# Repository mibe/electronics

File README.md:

# This repo contains some electronic projects of mine:

## Arduino
Some simple codes for the Arduino platform

## Blaulicht
Retrofitting an old toy car with emergency lights

## BreadBoard-Power-BusBar
Connect both opposing supply rails of a breadboard in an orderly fashion

## breakout_boards
Some breakout boards for use on a breadboard

## cookie-mouse
An automatic clicking mouse for the game Cookie Clicker

## Feuermelder
A USB "keyboard" disguised in the form of a fire call point to open the Windows Taskmanager

## Flip-USB
A replacement USB board for JBL's Flip 2 bluetooth speaker

## LCR-Shoe
A power supply attachment for cheap LCR meters

## StarPower
A control PCB for a christmas star as a replacement for the old, less energy-efficient one

## thunder-timer
A device to calculate thunderstorm distance by timing the interval between lightning and thunder

## tiny-UPDI-burner
A small board for connecting an USB to RS-232 converter to SOIC to DIL converters for burning ATtiny's via UPDI

## uCurrentCase
A case for Dave Jones' µCurrent GOLD

## USB-breaker
A tool to shortly disconnect a USB device from the USB bus

## Wire-to-RJ14
A simple adapter to connect bare wires to a cable with RJ-14 connectors

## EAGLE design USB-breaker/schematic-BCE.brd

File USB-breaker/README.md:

# USB-breaker
This is a tool to shortly disconnect a USB device from the USB bus. This is done by switching two relays, which are tied into the USB bus. One relay switches the data lines, the other the power supply lines. A RC filter tries to mimic the unplugging of a USB type A connector: Due to the design of this connector, the data lines are disconnected before the power lines.

This tool is mainly used for developing USB devices: A reset is now possible without unplugging the USB connector of the device. Hence it is saving insertion-removal cycles of the hub's USB connector: The standard A type connector has a designed lifetime of 1.500 cycles (see "Universal Serial Bus Cables and Connectors Class Document", table 3-1).

## BOM

### PCB
See the ```BOM-PCB.csv``` file. Short summary:

* 2 capacitors
* 2 diodes
* 1 pin header
* 2 relays
* 5 resistors
* 2 transistors
* 5 connectors

### The rest
* Case KEMO G025
* Red LED, 3 mm diameter
* SPST switch (on/off switch)
* Push button, normally open
* Some wires
* Four 5 mm spacer bolts
* Four M3 5 mm screws

## Enclosure
The top half of the case is used as front panel, where the controls and indicator LED are mounted. See ```drilling plan.pdf``` for a drawing of the drill holes. 

## Limitations
This tool is not designed to work with high-current USB devices. It is designed for a standard USB device with draws 500 mA at maximum. Don't hook up a device which draws more current (like a phone, charger, fan or vacuum cleaner)! The rated load of the relay contacts is 1 A, though.

## Design & building remarks
* If you don't have an SPST switch, you can use any other and just leave the remaining pole(s) unconnected.
* It was planned to connect the front panel with ribbon cable & an IDC connector mating with ```SV1```. But that didn't work, because the switch got in the way. Use a case which is at least 1.5 cm higher.
* Use the -ECB.brd / -ECB.sch files if you have transistors with a different pinout.

## License
GNU GPL v2 (see LICENSE.txt and firmware/usbdrv/License.txt)

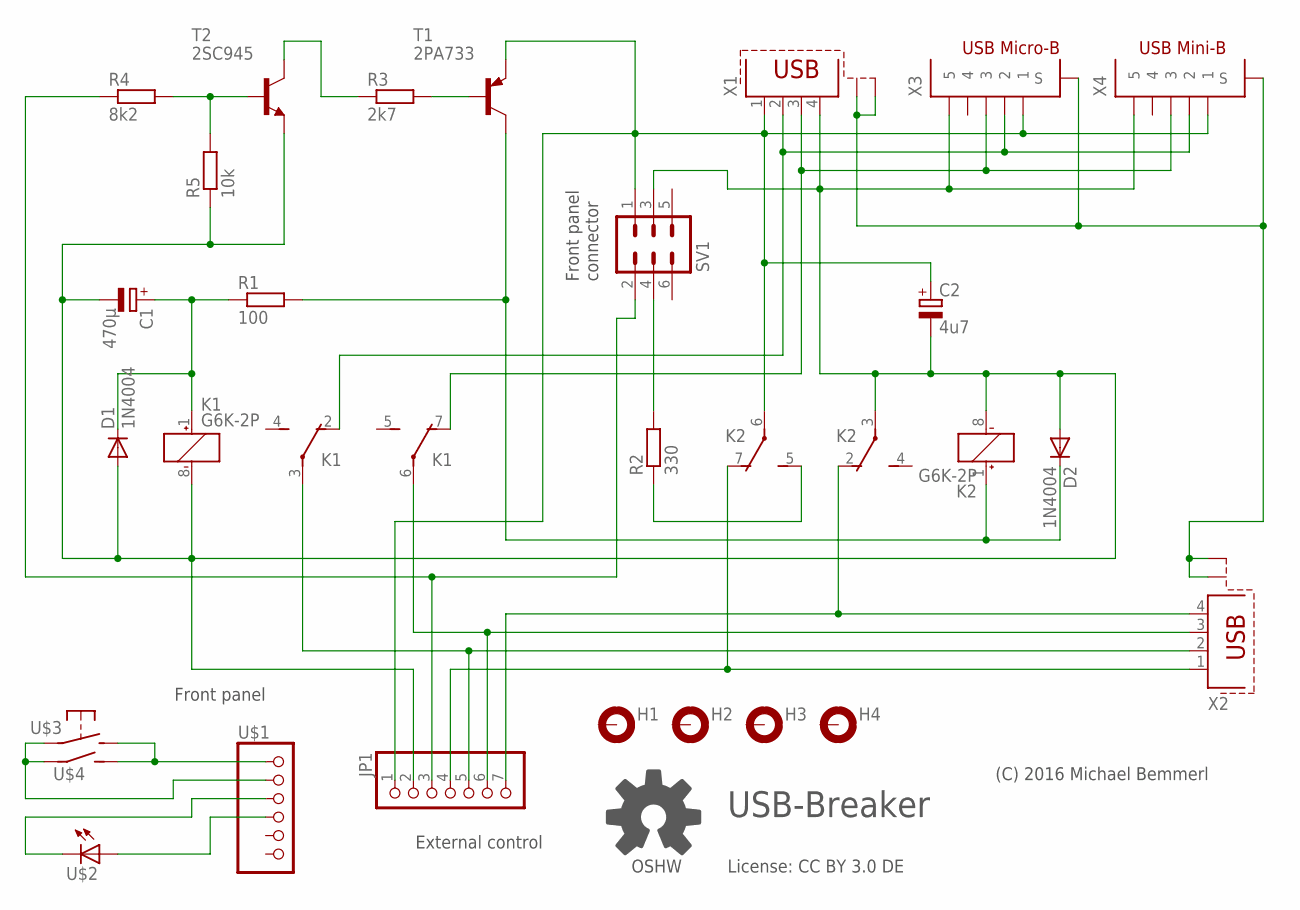
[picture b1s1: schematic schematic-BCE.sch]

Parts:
C1: 470µ; E3,5-8
C2: 4u7; E2,5-6
D1, D2: 1N4004; DO41-10
H1, H2, H3, H4: MOUNT-PAD-ROUND3.0; 3,0-PAD
JP1: PINHD-1X7/90; 1X07/90
K1, K2: G6K-2P
R1: 100; 0207/10
R2: 330; 0207/10
R3: 2k7; 0207/10
R4: 8k2; 0207/10
R5: 10k; 0207/10
SV1: ML6
T1: 2PA733; TO92-BCE
T2: 2SC945; TO92-ECB
X1: PN61729-S
X2: PN87520-S
X3: 10104110; 10104110-0001LF
X4: UX60SC-MB-5ST

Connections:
D+_IN: K1.7 (O), X1.3, X3.P$3 (3), X4.P$3 (3)
D+_OUT: JP1.6, K1.6, X2.3
D-_IN: K1.2 (O), X1.2, X3.P$2 (2), X4.P$2 (2)
D-_OUT: JP1.5, K1.3, X2.2
ENABLE: D2.C, K2.1 (+), R1.2, T1.C
EXTERNAL_ENABLE: JP1.3, R4.1, SV1.2
GND_IN: C1.-, C2.-, D1.A, D2.A, JP1.2, K1.8 (-), K2.3, K2.8 (-), R5.1, SV1.3, T2.E, X1.4, X3.P$5 (5), X4.P$5 (5)
GND_OUT: JP1.7, K2.2 (O), X2.4
LED: R2.2, SV1.4
unnamed: R3.2, T1.B
unnamed: R3.1, T2.C
unnamed: R4.2, R5.2, T2.B
unnamed: C1.+, D1.C, K1.1 (+), R1.1
SHIELD: X1.S1, X1.S2, X2.S1, X2.S2, X3.P$6 (S), X3.P$7 (S), X4.P$6 (S), X4.P$7 (S)
VCC_IN: C2.+, JP1.1, K2.6, SV1.1, T1.E, X1.1, X3.P$1 (1), X4.P$1 (1)
VCC_LED: K2.5 (S), R2.1
VCC_OUT: JP1.4, K2.7 (O), X2.1

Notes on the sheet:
Front panel
Front panel connector
External control
OSHW
(C) 2016 Michael Bemmerl
License: CC BY 3.0 DE
USB-Breaker

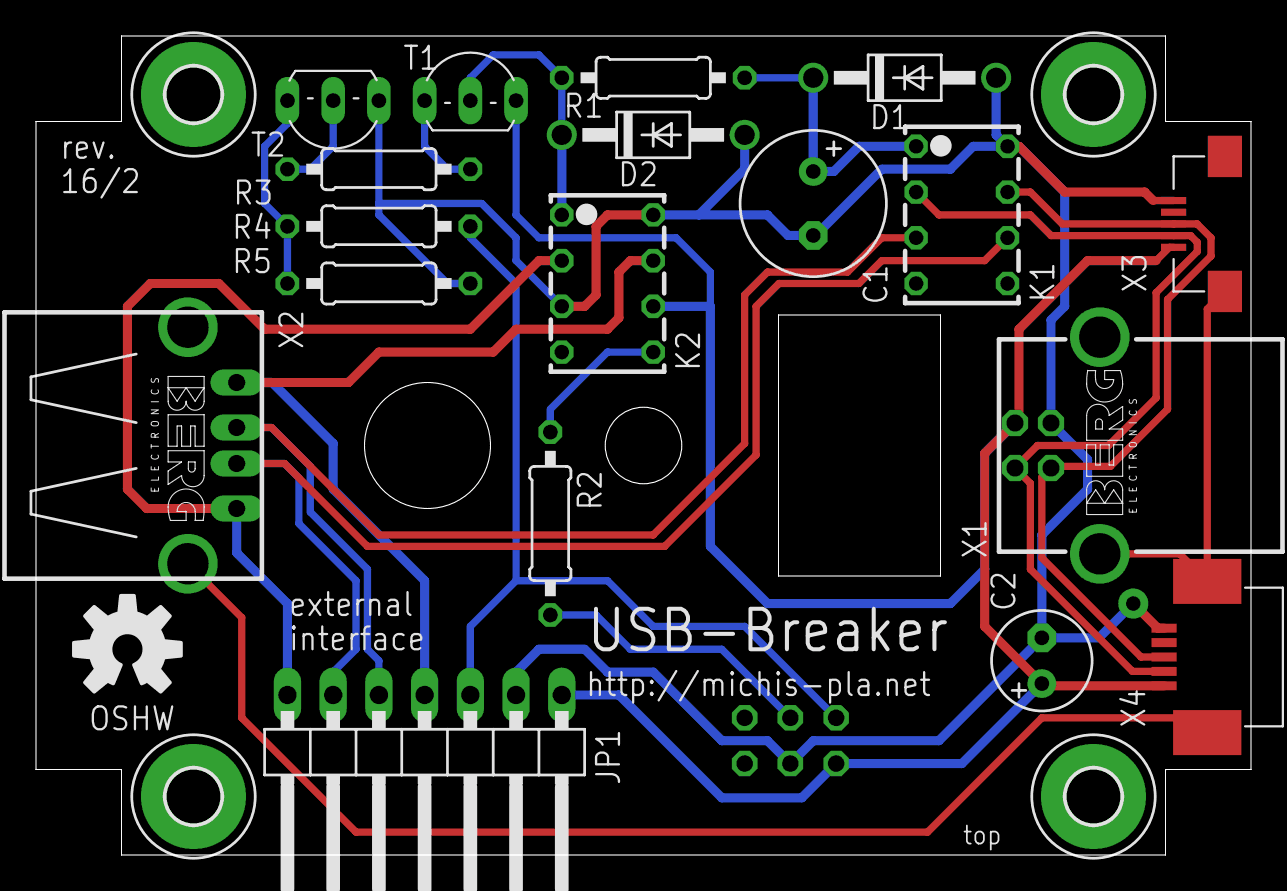
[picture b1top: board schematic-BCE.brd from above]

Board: 2 copper layers, 67.5 x 45.5 mm, 23 parts (1 on the bottom side), 17 nets.

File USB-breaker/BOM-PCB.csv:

"Part";"Value";"Device";"Package";"Description"
"C1";"470µ";"CPOL-EUE3.5-8";"E3,5-8";"POLARIZED CAPACITOR, European symbol"
"C2";"4u7";"CPOL-EUE2.5-6";"E2,5-6";"POLARIZED CAPACITOR, European symbol"
"D1";"1N4004";"1N4004";"DO41-10";"DIODE"
"D2";"1N4004";"1N4004";"DO41-10";"DIODE"
"H1";"MOUNT-PAD-ROUND3.0";"MOUNT-PAD-ROUND3.0";"3,0-PAD";"MOUNTING PAD, round"
"H2";"MOUNT-PAD-ROUND3.0";"MOUNT-PAD-ROUND3.0";"3,0-PAD";"MOUNTING PAD, round"
"H3";"MOUNT-PAD-ROUND3.0";"MOUNT-PAD-ROUND3.0";"3,0-PAD";"MOUNTING PAD, round"
"H4";"MOUNT-PAD-ROUND3.0";"MOUNT-PAD-ROUND3.0";"3,0-PAD";"MOUNTING PAD, round"
"JP1";"";"PINHD-1X7/90";"1X07/90";"PIN HEADER"
"K1";"G6K-2P";"G6K-2P";"G6K-2P";"Low Signal Relay"
"K2";"G6K-2P";"G6K-2P";"G6K-2P";"Low Signal Relay"
"R1";"100";"R-EU_0207/10";"0207/10";"RESISTOR, European symbol"
"R2";"330";"R-EU_0207/10";"0207/10";"RESISTOR, European symbol"
"R3";"2k7";"R-EU_0207/10";"0207/10";"RESISTOR, European symbol"
"R4";"8k2";"R-EU_0207/10";"0207/10";"RESISTOR, European symbol"
"R5";"10k";"R-EU_0207/10";"0207/10";"RESISTOR, European symbol"
"SV1";"";"ML6";"ML6";"HARTING"
"T1";"BC558B";"BC558B-PNP-TO92-EBC";"TO92-EBC";"PNP Transistror"
"T2";"BC548B";"BC548-NPN-TO92-CBE";"TO92-CBE";"NPN Transistror"
"X1";"PN61729-S";"PN61729-S";"PN61729-S";"BERG USB connector"
"X2";"PN87520-S";"PN87520-S";"PN87520-S";""
"X3";"10104110";"10104110";"10104110-0001LF";"10104110 - Micro USB B Type Receptacle"
"X4";"UX60SC-MB-5ST";"UX60SC-MB-5ST";"UX60SC-MB-5ST";"UX60S Series - Mini-B Connectors, SMT mount receptacles meeting requirements of USB 2.0 Standard"

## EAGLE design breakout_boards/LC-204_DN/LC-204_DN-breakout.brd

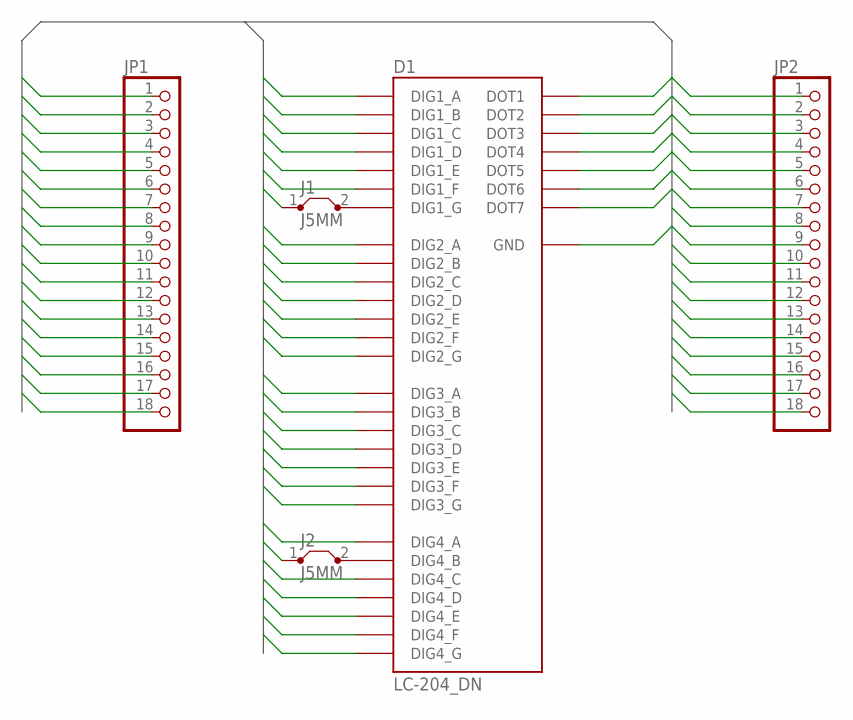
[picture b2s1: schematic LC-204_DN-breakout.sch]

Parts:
D1: LC-204_DN
J1, J2: J5MM; 05
JP1, JP2: PINHD-1X18; 1X18

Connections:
DIG1_1: D1.DIG1_A, JP2.4
DIG1_2: D1.DIG1_B, JP2.5
DIG1_3: D1.DIG1_C, JP1.4
DIG1_4: D1.DIG1_D, JP1.3
DIG1_5: D1.DIG1_E, JP1.2
DIG1_6: D1.DIG1_F, JP2.3
DIG1_7: J1.1, JP2.2
DIG2_1: D1.DIG2_A, JP2.8
DIG2_2: D1.DIG2_B, JP2.9
DIG2_3: D1.DIG2_C, JP1.7
DIG2_4: D1.DIG2_D, JP1.6
DIG2_5: D1.DIG2_E, JP1.5
DIG2_6: D1.DIG2_F, JP2.7
DIG2_7: D1.DIG2_G, JP2.6
DIG3_1: D1.DIG3_A, JP2.12
DIG3_2: D1.DIG3_B, JP2.13
DIG3_3: D1.DIG3_C, JP1.12
DIG3_4: D1.DIG3_D, JP1.11
DIG3_5: D1.DIG3_E, JP1.9
DIG3_6: D1.DIG3_F, JP2.11
DIG3_7: D1.DIG3_G, JP1.10
DIG4_1: D1.DIG4_A, JP2.16
DIG4_2: J2.1, JP2.17
DIG4_3: D1.DIG4_C, JP1.16
DIG4_4: D1.DIG4_D, JP1.15
DIG4_5: D1.DIG4_E, JP1.14
DIG4_6: D1.DIG4_F, JP2.15
DIG4_7: D1.DIG4_G, JP2.14
DOT1: D1.DOT1, JP2.1
DOT2: D1.DOT2, JP1.1
DOT3: D1.DOT3, JP2.10
DOT4: D1.DOT4, JP1.8
DOT5: D1.DOT5, JP1.13
DOT6: D1.DOT6, JP2.18
DOT7: D1.DOT7, JP1.17
GND: D1.GND, JP1.18
unnamed: D1.DIG1_G, J1.2
unnamed: D1.DIG4_B, J2.2

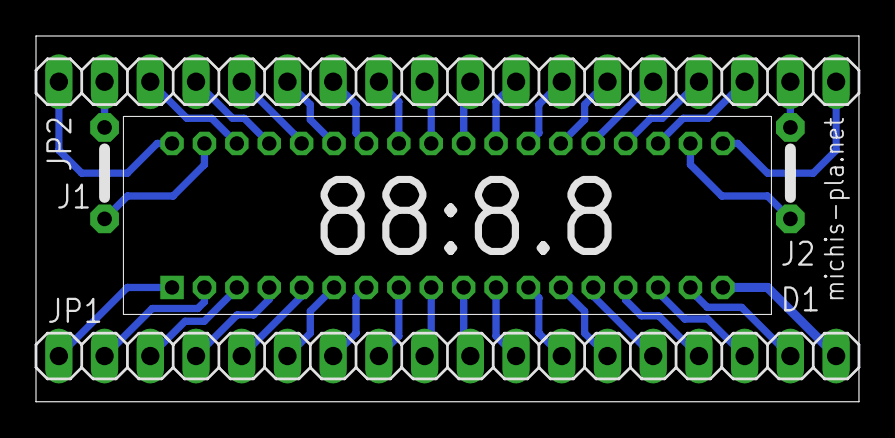
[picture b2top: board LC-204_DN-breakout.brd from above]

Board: 2 copper layers, 45.7 x 20.3 mm, 5 parts (0 on the bottom side), 38 nets.

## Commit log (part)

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2012-10-24 Two types of blinking (static / random)
2012-10-24 Moved definitions into separate header file.
2012-10-27 Another blink mode, this time on and off time are random.
2012-10-27 Updated .gitignore to ignore AVR Studio workspace files (*.aws).
2012-11-18 Added schematics.
2013-01-26 Web frontend supports more than one sensor
2013-01-27 Output temperature on LCD via RS-232
2013-01-27 Interrupt logic for button; Moved LCD pins to < 10, because >= 10 is SPI for Ethernet shield
2013-01-27 Fixed delay logic (overflow)
2013-01-27 Read VCC for use in calculation of LM35 value
2013-01-31 Reactivated ethernet functions. This should be it for the 2013 version of this project.
2013-08-26 All EEVblog episodes with youtube URLs
2014-03-24 EEVblog YouTube episode URLs updated
2015-05-10 Added V-USB driver from release 20121206
2015-05-15 Working Makefile & USB config
    Both were generated by the make-file.sh script
2015-05-16 Use the calibration routine for the RC oscillator.
2015-05-16 Changed Makefile for specific ATTiny45 configuration.
2015-05-17 Removed the demo circle function and added code for activating the mouse button depending on the switch state.
2015-05-31 Use Timer1 overflow for activating the mouse button
2015-06-07 Bugfix: Prevent the disabling of Timer1 when the ADC value is too low.
2015-06-07 Use the full scale of the potentiometer in the ADC IRQ.
2015-06-08 Mostly license stuff
2015-06-09 Added README and circuit diagram.
2015-06-10 Tested with Linux kernel OS
2015-06-10 Added switch and push button, connected to ground.
2015-06-11 Screenshot of the circuit diagram
2015-12-06 Replaced K1 & K2 relay G6K-RF with G6K-2P. SMD --> THT
2016-01-23 Display only pin names in symbol UX60S.
2016-01-24 Using shielded A connectors now.
2016-01-24 Bugfix: Connect the delayed relay to GND_IN instead of the (already disconnected off) GND_OUT.
2016-01-24 Completed front panel components.
2016-02-16 New external control interface as pin header.
2016-02-16 Switching of the relays is done upstream with transistors.
    Also finished connecting nets to the external interface connector.
2016-02-19 The schematic is now pretty much done:
    - Library update
    - Values for the two transistors
2016-02-20 Added last details:
    - Name / Copyright / License
    - OSHW logo
    - Processed all warnings in the ERC
    Boy, this schematic looks ugly. I'm better using a DIN A4 frame next time...
2016-02-21 Basic PCB dimensioning
2016-02-23 First parts placed
2016-03-02 NAME and VALUE on wrong layer
2016-03-06 Shield pins of both USB connectors are marked as internally connected.
2016-03-06 PCB layout, part one
2016-03-08 Added signal classes for USB data and power.
2016-03-11 Added VCC_OUT & GND_OUT to power signal class
2016-03-13 Changed text ratio.
2016-03-13 Say hello to Mr. Ground Plane!
2016-03-20 Breakout board for a Rohm LC204 DN LED 7-segment display.
2016-04-23 Value of R1 changed from 120 Ω to 100 Ω. Otherwise the voltage for relay K1 is too low.
2016-04-23 T1 is now used from another library. BCE was wrong, ECB is the right package.
2016-04-24 The first assembly pics.
2016-04-30 Added code from V-USB HIDKeys example, release 2012-12-08.
2016-05-01 Changed USB settings:
    - using pid.codes' test PID
    - correct report descriptor length
    - changed device name
    - using INTR_POLL_INTERVAL from HIDKeys example
2016-05-09 Don't call buildReport on USBRQ_HID_GET_REPORT - just relay the previous generated one.
2016-05-10 Removed unused #define's and converted spaces used as indentation to tabs.
2016-05-10 License stuff
2016-05-10 Added a README.md.
2016-05-10 PID 0xF12E got assigned by pid.codes. Thanks!
2016-06-02 Bugfix: USB D- was wrongly connected to PB1 instead of PB2.
2016-06-08 Updated screenshot of Feuermelder schematic
2016-06-11 Added README and BOM.
2016-06-11 Added two photographs of the finished device.
2016-06-11 Updated the README.
2018-01-03 New device: MTCH101 (touch sensor IC)
2018-01-14 New device: TS3USB30E (High-Speed USB 2.0 Multiplexer)
2018-01-30 Who the hell thought it would be a good idea to force net names on pins marked as sup?
2018-02-05 New device: CLP6C RGB LED
2018-03-02 Fixed layer
2018-06-03 Looks like the timing algorithm is working.
2018-07-06 Moved Eagle CAD library to new folder and added a KiCad library.
2018-07-09 The schematic should be complete now.
2018-07-13 Added courtyard for part SW_Push_10mm.
2018-07-14 Added ground plane
2018-08-01 Readme and license stuff
2018-08-08 Oops, debugging stuff was still in the code.
2018-08-08 Added comments
2018-08-19 That should be it for the schematic.
2018-08-25 The makefile...
2018-08-26 Added a reset switch.
2018-08-27 Renamed nets to some saner names.
2018-09-02 Finished the layout
2018-09-15 I got the pin-out of Q1 wrong: It's ECB not BCE!
2018-09-22 Added more documentation.
2018-09-29 Added some pictures
2018-10-08 Unlisted videos on EEVblog2
2019-05-05 Update files to KiCad 5
2019-05-11 Fixed update to KiCad 5.
    Well, the update didn't quite work out of the box. My footprint library table was still using the KiCad 4 footprints.
2019-05-27 Added a DC/DC converter to power the buzzer.
    The nominal battery voltage of 2.4 is too less for adequately powering the 5 volt buzzer. The converter provides provides 5 volt exclusively for the buzzer and is enabled by the microcontroller.
2019-06-10 Updated PCB rendering to current revision
2019-06-14 Deactivated the BOD again.
    Well, that didn't quite work out: The BOD was erroneously triggered during activation of the buzzer. The input voltage probably had a transient which caused the trigger.
2019-06-23 Beep every kilometer when counting.
    This implements #3.
2019-09-10 Bunch o' footprints:
    - USB connectors
    - Battery contacts / holders
2019-10-16 Renamed some nets and added mounting holes.
2019-10-19 Renamed to add suffix CircularHoles.
2019-10-26 Marker of the PCB edge
2019-10-26 Import of the Aisler 2 layer template
2019-10-30 Routing and positioning of the silk screen elements is finished
2019-11-08 Removed unnecessary traces.
2019-11-11 Updated netlist
2020-01-18 Better description of the Keystone parts.
    The polarity is depending on how this connector is used.
    (cherry picked from commit 02e73c2f822f0898dfba0953576ab4aaca45f917)
2020-01-18 Rotated the Anti-Rotation Dimples by 45° clockwise.
    The datasheet states that the location is random, but all reference material I could find suggest that the dimples are 45° rotated to the datasheet version.
    (cherry picked from commit 67bc0c7df24bde9f7f3c4ad2011b5573b9a0d1f6)
2020-02-02 Marker of the PCB edge
    (cherry picked from commit 13fa41d590fd288d5f026ec3b4d3241c9ee901f3)
    # Conflicts:
    # Libraries/KiCad/mibe.pretty/BatteryHolder_MPD_BA9VPC_1xPP3.kicad_mod
2020-02-06 The footprints landed in the official KiCad footprint repository.
2020-02-18 Added BOM and "Characteristics" field for for more detail.
2020-02-18 Update LCR-Shoe.csv
    Let's see if GitHub displays this nice and beautiful...
2020-02-18 Update index
2020-02-19 USB B Lumberg 2411 02 updates
    Fixed Fab / Silk / CrtYrd layers, added 3D reference and prettified description.
2020-02-27 Fixed Silk and CrtYd layer.
2020-03-01 Centered footprint to origin @ 0,0.
2020-03-03 The main circuit.
2020-03-05 Fixed Fab layer line width.
2020-03-11 Moved the PCB to have the center at 127|127.
    This should make it easier to work with inch / millimeter.
2020-03-22 Removed more merged footprints
2020-03-29 The blinking algorithm is pretty much done.
    It uses both A & B channels of Timer0 in Fast PWM mode. Both channels are connected to their Output Compare pins. The Timer0 Overflow Interrupt powers a state machine, which in turn toggles the DDR b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
    The Timer0 controls the brightness of the LEDs with PWM, and the state machine controls the blinking pattern.
2020-03-31 Enter sleep mode as soon as the interrupt handling is finished.
2020-03-31 Disable stuff to minimize power consumption.
2020-04-17 Use a CR2032 3 Volt battery as power source.
2020-04-18 Enable pull-ups on unsused inputs.
2020-04-19 Optimized the code a bit. This saves a couple of decibytes.
2020-05-13 Added Readme.md
2020-05-17 Moved the headers by about 0.5 mm.
    The previous distance was too small and the headers didn't fit properly into the breadboard.
2020-05-30 Added components to have a power status LED on the PCB.
2020-05-31 Finished placing and routing the new components for the Power indication.
2020-06-02 Added BOM.
2020-06-02 Added a readme file.
2020-06-02 Updated URL to CERN OHL v1.2 license.
2020-06-03 Open Source Hardware Logo in 2.7 x 2.5 mm size.
2020-06-08 Added a reverse protection diode.
2020-06-10 Another variant of the OSHW logo.
2020-06-19 Fix typo.
2021-02-23 Wire-to-RJ14, a board for connecting bare wires to an RJ14 connector used in POTS.
2021-08-08 Add a replacement USB board for JBL's Flip 2 bluetooth speaker.
2021-08-28 First bits of the Magic the Gathering life counter.
2021-09-07 Use Timer0 for multiplexing both 7-segment-digits.
2021-10-04 The PCB is done, except for the Silk layer.
2021-10-11 The silk layer is now done. Also added a BOM.
2021-11-03 First bits of the schematic of the PCB.
2021-11-08 Specify programming resistor and protection diode for charger.
2021-11-09 Add a voltage monitor to be used to reset the microcontroller.
    This is used as sort of a undervoltage lockout protection to protect the battery. The threshold voltage of the used IC is 3.08 V, which is near the minimum discharge voltage of a LiPo battery of 3 V.
2021-11-28 Reset circuitry
2021-11-29 Add digit multiplexing.
2021-12-08 Use a net tie for combining MOSI/MISO & DIGIT_X_ENABLE.
    MOSI/MISO are used for programming, while the DIGIT_X_ENABLE lines enable the corresponding display digit.
    That's pretty much it for the schematic. Finally.
2021-12-21 First bits of the PCB layout.
2022-07-08 Placement of (mounting) holes, 7-seg. displays and programming socket.
2022-07-18 The placing & routing is pretty much done, except GND.
2022-07-19 All references are moved to a visible location.
2022-07-19 Improved the silkscreen a bit.
2022-08-03 Add BOM HTML file.
2022-09-20 Add missing parenthesis.
    This explains the unwanted (and not programmed) behavior discussed in #10.
2022-10-08 Display sizes with percentages of used space.
2022-10-25 Prevent "afterglow" of the digits by decreasing the multiplexing speed.
    Instead of using the full clock, a prescaler of 64 is used now.
2022-10-25 Fixed various stuff:
    - The counting function now works properly (fixed #9)
    - When multiplexing the correct digit is driven
    - More comments here and there
2022-11-01 Remove R16 to fix #8.
    The chances of the battery and programmer connected at the same time is there but actually pretty low. To flash the micro-controller you would disconnect the battery because of the easier handling al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
2022-11-02 Change the USB B mini charging connector to USB C (see #6). Still needs to be placed and routed.
2022-11-12 Add first version of the schematic.
2022-11-14 Add mounting holes and the correct footprint for the push button.
2022-11-14 Starting with layout: Components which have fixed positions due to the casing are placed and locked.
2022-11-16 Bugifx: The crystal footprint had the wrong pin mapping.
2022-11-16 Finish the layout of the first revision.
2022-11-22 Add BOM
2022-11-26 Optimized the code a bit to consume less CPU cycles in Timer mode.
2022-11-27 Disable stuff to save power:
    - Enter sleep mode
    - Disable Timer0, USI, ADC, the analog comparator & digital input buffer.
    - Enable pull-ups
2022-11-27 Use Timer0 as timer instead of Timer1.
    Timer0 consumes less power than Timer1. That saves a whopping 4 µA, which is 25.6 %! This has some serious Apollo 13 vibes!
2022-11-28 Enable the pull-up on the button pin only.
    The free pins are connected to Ground on the PCB.
2022-11-28 Changed microcontroller footprint of U1, and using the low voltage type now.
2022-11-28 Add a readme.
2022-12-04 Add some pictures of the StarPower PCB assembled.
2022-12-11 USB C connector placed and routed.
    This fixes #6.
2023-01-17 Display a "dEAd" animation on the 7-segment display if the player counter reached 0.
2023-01-25 Some cleanup...
2023-03-08 Rename variable
2023-04-02 Put constant stuff into program memory to safe some of the precious RAM!
    MY PRECIOUS!
